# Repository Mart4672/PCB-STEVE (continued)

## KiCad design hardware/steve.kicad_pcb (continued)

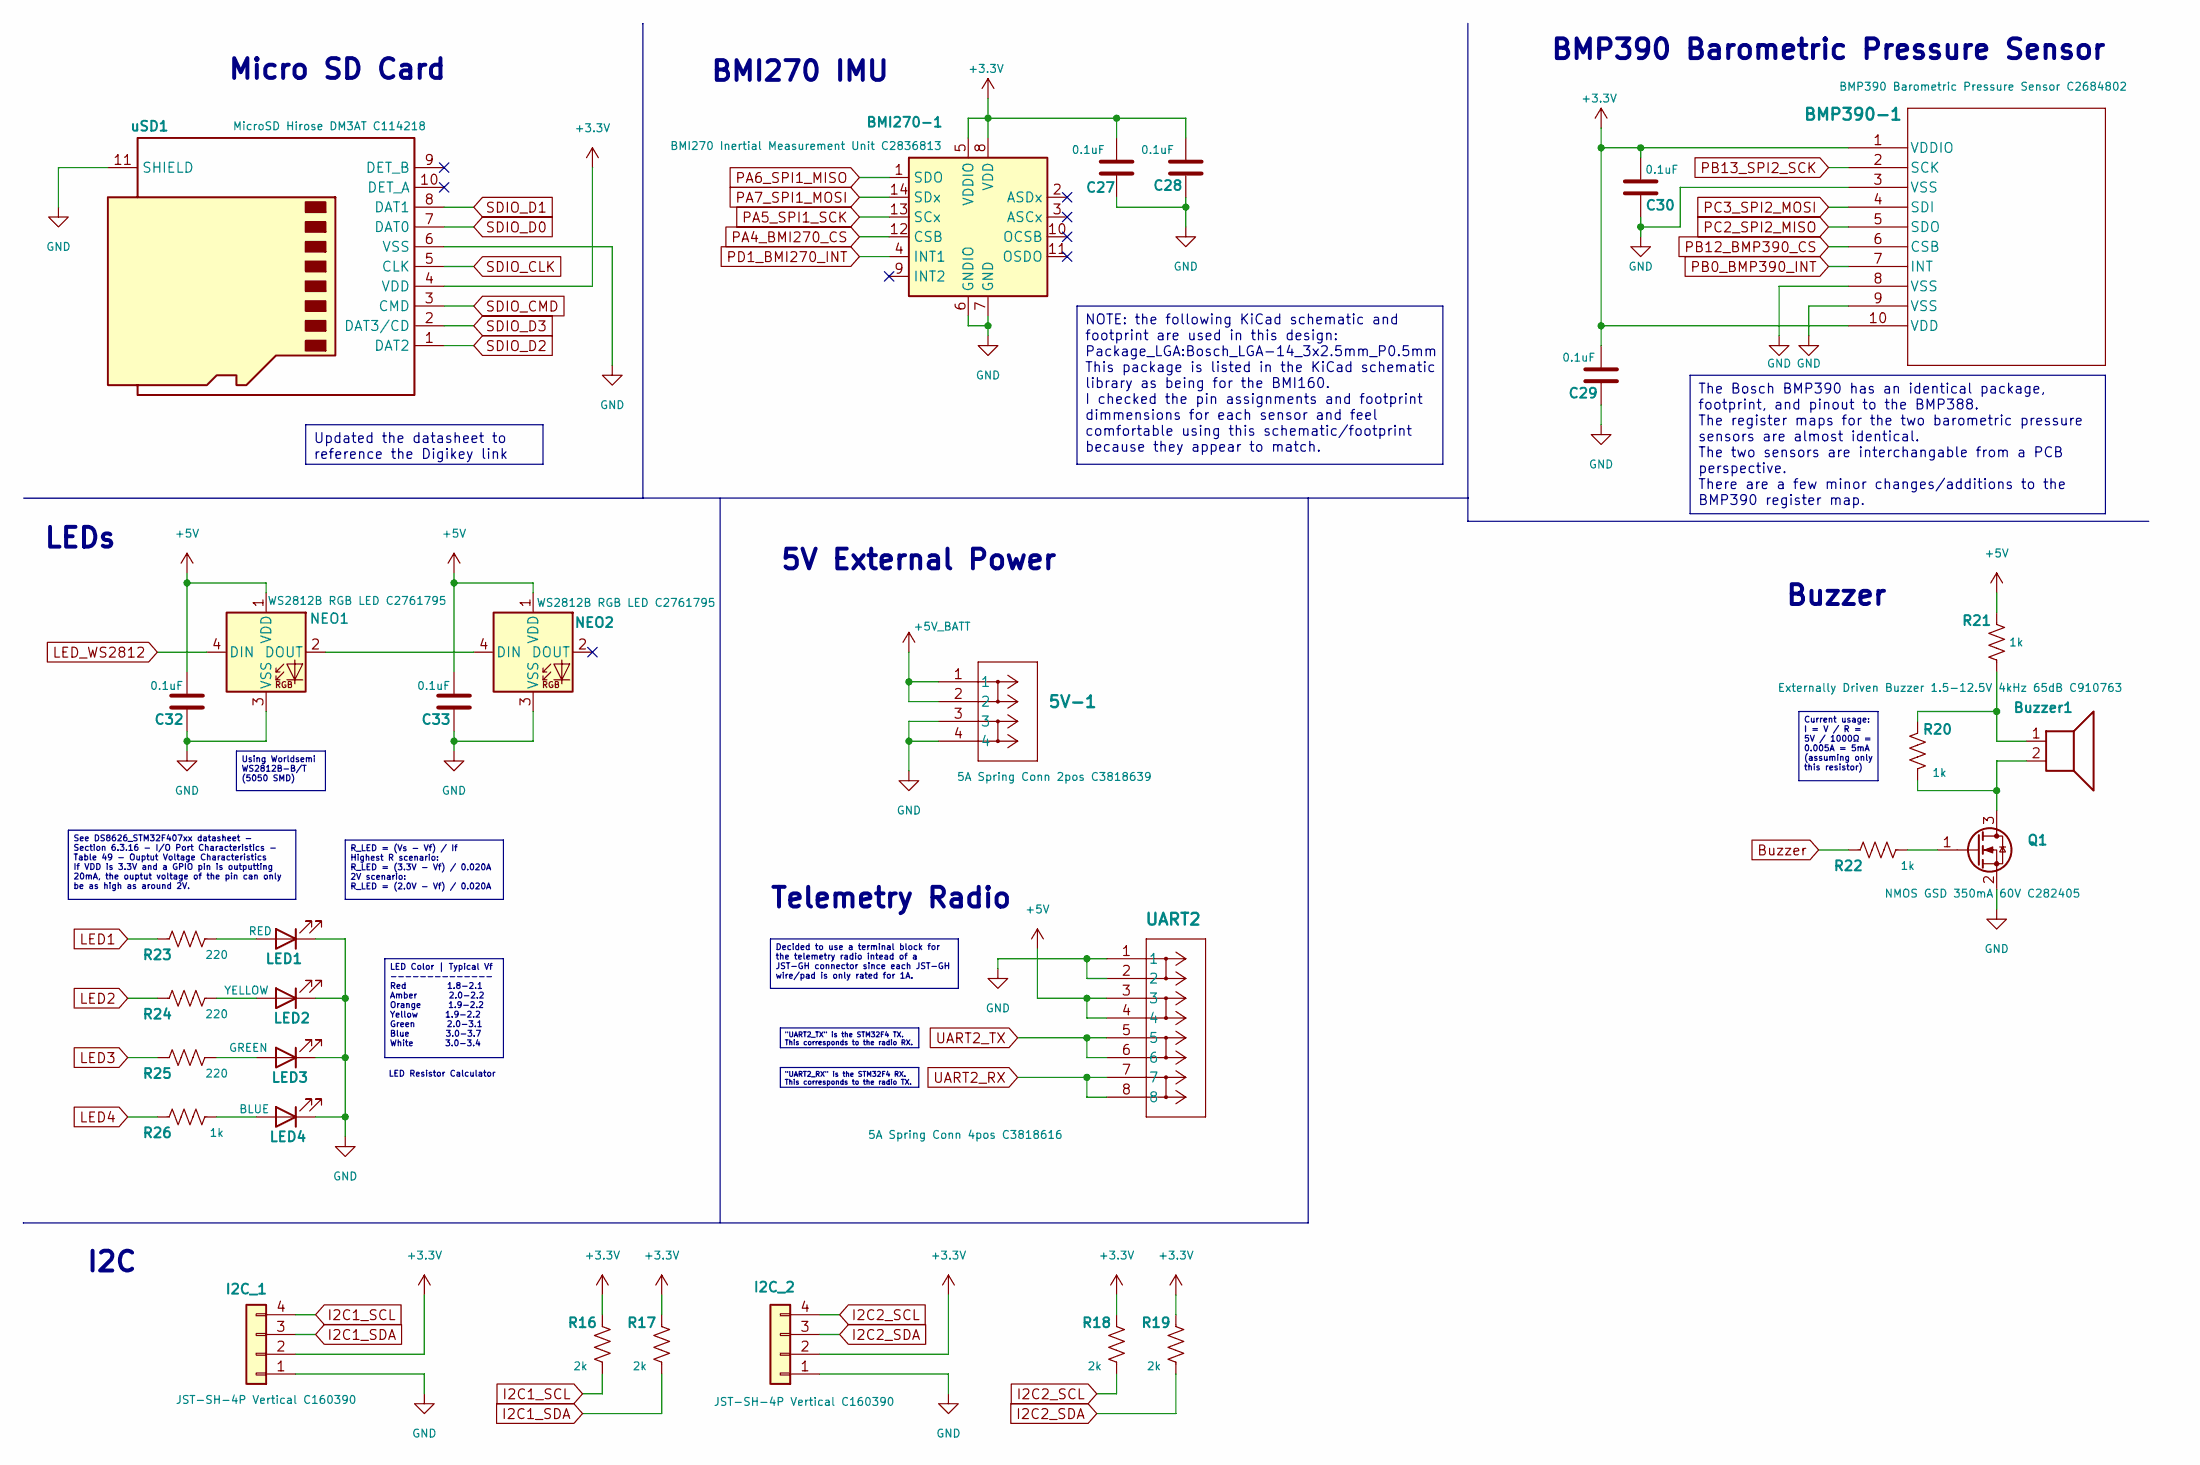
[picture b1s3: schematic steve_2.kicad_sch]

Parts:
5V-1: 5A Spring Conn 2pos C3818639; CONN_1814498_TerminalBlock-1770885-2pos
BMI270-1: BMI270 Inertial Measurement Unit C2836813; Bosch_LGA-14_3x2.5mm_P0.5mm
BMP390-1: BMP390 Barometric Pressure Sensor C2684802; QFN_BMP388_BOS
Buzzer1: Externally Driven Buzzer 1.5-12.5V 4kHz 65dB C910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; Buzzer_Murata_PKMCS0909E
C27, C28, C29, C30, C32, C33: 0.1uF; C_0603_1608Metric
I2C_1, I2C_2: JST-SH-4P Vertical C160390; JST-SH_BM04B-SRSS-TB_1x04_Vertical_P1.00mm
LED1: RED; LED_0603_1608Metric
LED2: YELLOW; LED_0603_1608Metric
LED3: GREEN; LED_0603_1608Metric
LED4: BLUE; LED_0603_1608Metric
NEO1, NEO2: WS2812B RGB LED C2761795; LED_WS2812B_PLCC4_5.0x5.0mm_P3.2mm
Q1: NMOS GSD 350mA 60V C282405; SOT-23
R16, R17, R18, R19: 2k; R_0603_1608Metric
R20, R21, R22, R26: 1k; R_0603_1608Metric
R23, R24, R25: 220; R_0603_1608Metric
UART2: 5A Spring Conn 4pos C3818616; CONN_1814582_TerminalBlock_1770979_4pos_Vertical
uSD1: MicroSD Hirose DM3AT C114218; microSD_3D_HC_Hirose_DM3AT-SF-PEJM5

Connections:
+3.3V: BMI270-1.5 (VDDIO), BMI270-1.8 (VDD), BMP390-1.1 (VDDIO), BMP390-1.10 (VDD), C27.1, C28.1, C29.1, C30.1, I2C_1.2, I2C_2.2, R16.2, R17.2, R18.2, R19.2, uSD1.4 (VDD); also elsewhere on the board
+5V: C32.1, C33.1, NEO1.1 (VDD), NEO2.1 (VDD), R21.2, UART2.3, UART2.4; also elsewhere on the board
+5V_BATT: 5V-1.1, 5V-1.2; also elsewhere on the board
Buzzer: R22.1; also elsewhere on the board
GND: 5V-1.3, 5V-1.4, BMI270-1.6 (GNDIO), BMI270-1.7 (GND), BMP390-1.3 (VSS), BMP390-1.8 (VSS), BMP390-1.9 (VSS), C27.2, C28.2, C29.2, C30.2, C32.2, C33.2, I2C_1.1, I2C_2.1, LED1.1 (K), LED2.1 (K), LED3.1 (K), LED4.1 (K), NEO1.3 (VSS), NEO2.3 (VSS), Q1.2 (S), UART2.1, UART2.2, uSD1.6 (VSS), uSD1.11 (SHIELD); also elsewhere on the board
I2C1_SCL: I2C_1.4, R16.1; also elsewhere on the board
I2C1_SDA: I2C_1.3, R17.1; also elsewhere on the board
I2C2_SCL: I2C_2.4, R18.1; also elsewhere on the board
I2C2_SDA: I2C_2.3, R19.1; also elsewhere on the board
LED1: R23.1; also elsewhere on the board
LED2: R24.1; also elsewhere on the board
LED3: R25.1; also elsewhere on the board
LED4: R26.1; also elsewhere on the board
LED_WS2812: NEO1.4 (DIN); also elsewhere on the board
unnamed: Buzzer1.1, R20.2, R21.1
unnamed: LED1.2 (A), R23.2
unnamed: LED2.2 (A), R24.2
unnamed: LED3.2 (A), R25.2
unnamed: LED4.2 (A), R26.2
unnamed: NEO1.2 (DOUT), NEO2.4 (DIN)
unnamed: Buzzer1.2, Q1.3 (D), R20.1
unnamed: Q1.1 (G), R22.2
PA4_BMI270_CS: BMI270-1.12 (CSB); also elsewhere on the board
PA5_SPI1_SCK: BMI270-1.13 (SCx); also elsewhere on the board
PA6_SPI1_MISO: BMI270-1.1 (SDO); also elsewhere on the board
PA7_SPI1_MOSI: BMI270-1.14 (SDx); also elsewhere on the board
PB0_BMP390_INT: BMP390-1.7 (INT); also elsewhere on the board
PB12_BMP390_CS: BMP390-1.6 (CSB); also elsewhere on the board
PB13_SPI2_SCK: BMP390-1.2 (SCK); also elsewhere on the board
PC2_SPI2_MISO: BMP390-1.5 (SDO); also elsewhere on the board
PC3_SPI2_MOSI: BMP390-1.4 (SDI); also elsewhere on the board
PD1_BMI270_INT: BMI270-1.4 (INT1); also elsewhere on the board
SDIO_CLK: uSD1.5 (CLK); also elsewhere on the board
SDIO_CMD: uSD1.3 (CMD); also elsewhere on the board
SDIO_D0: uSD1.7 (DAT0); also elsewhere on the board
SDIO_D1: uSD1.8 (DAT1); also elsewhere on the board
SDIO_D2: uSD1.1 (DAT2); also elsewhere on the board
SDIO_D3: uSD1.2 (DAT3/CD); also elsewhere on the board
UART2_RX: UART2.7, UART2.8; also elsewhere on the board
UART2_TX: UART2.5, UART2.6; also elsewhere on the board

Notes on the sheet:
BMP390 Barometric Pressure Sensor
Micro SD Card
LEDs
BMI270 IMU
5V External Power
LED Resistor Calculator
Buzzer
Telemetry Radio
I2C
LED Color | Typical Vf -------------- Red 1.8-2.1 Amber 2.0-2.2 Orange 1.9-2.2 Yellow 1.9-2.2 Green 2.0-3.1 Blue 3.0-3.7 White 3.0-3.4
See DS8626_STM32F407xx datasheet - Section 6.3.16 - I/O Port Characteristics - Table 49 - Ouptut Voltage Characteristics If VDD is 3.3V and a GPIO pin is outputting 20mA, the ouptut voltage of the pin can only be as high as around 2V.
Using Worldsemi WS2812B-B/T (5050 SMD)
Decided to use a terminal block for the telemetry radio intead of a JST-GH connector since each JST-GH wire/pad is only rated for 1A.
"UART2_TX" is the STM32F4 TX. This corresponds to the radio RX.
Current usage: I = V / R = 5V / 1000Ω = 0.005A = 5mA (assuming only this resistor)
NOTE: the following KiCad schematic and footprint are used in this design: Package_LGA:Bosch_LGA-14_3x2.5mm_P0.5mm This package is listed in the KiCad schematic library as being for the BMI160. I checked the pin assignments and footprint dimmensions for each sensor and feel comfortable using this s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
Updated the datasheet to reference the Digikey link
"UART2_RX" is the STM32F4 RX. This corresponds to the radio TX.
The Bosch BMP390 has an identical package, footprint, and pinout to the BMP388. The register maps for the two barometric pressure sensors are almost identical. The two sensors are interchangable from a PCB perspective. There are a few minor changes/additions to the BMP390 register map.
R_LED = (Vs - Vf) / If Highest R scenario: R_LED = (3.3V - Vf) / 0.020A 2V scenario: R_LED = (2.0V - Vf) / 0.020A

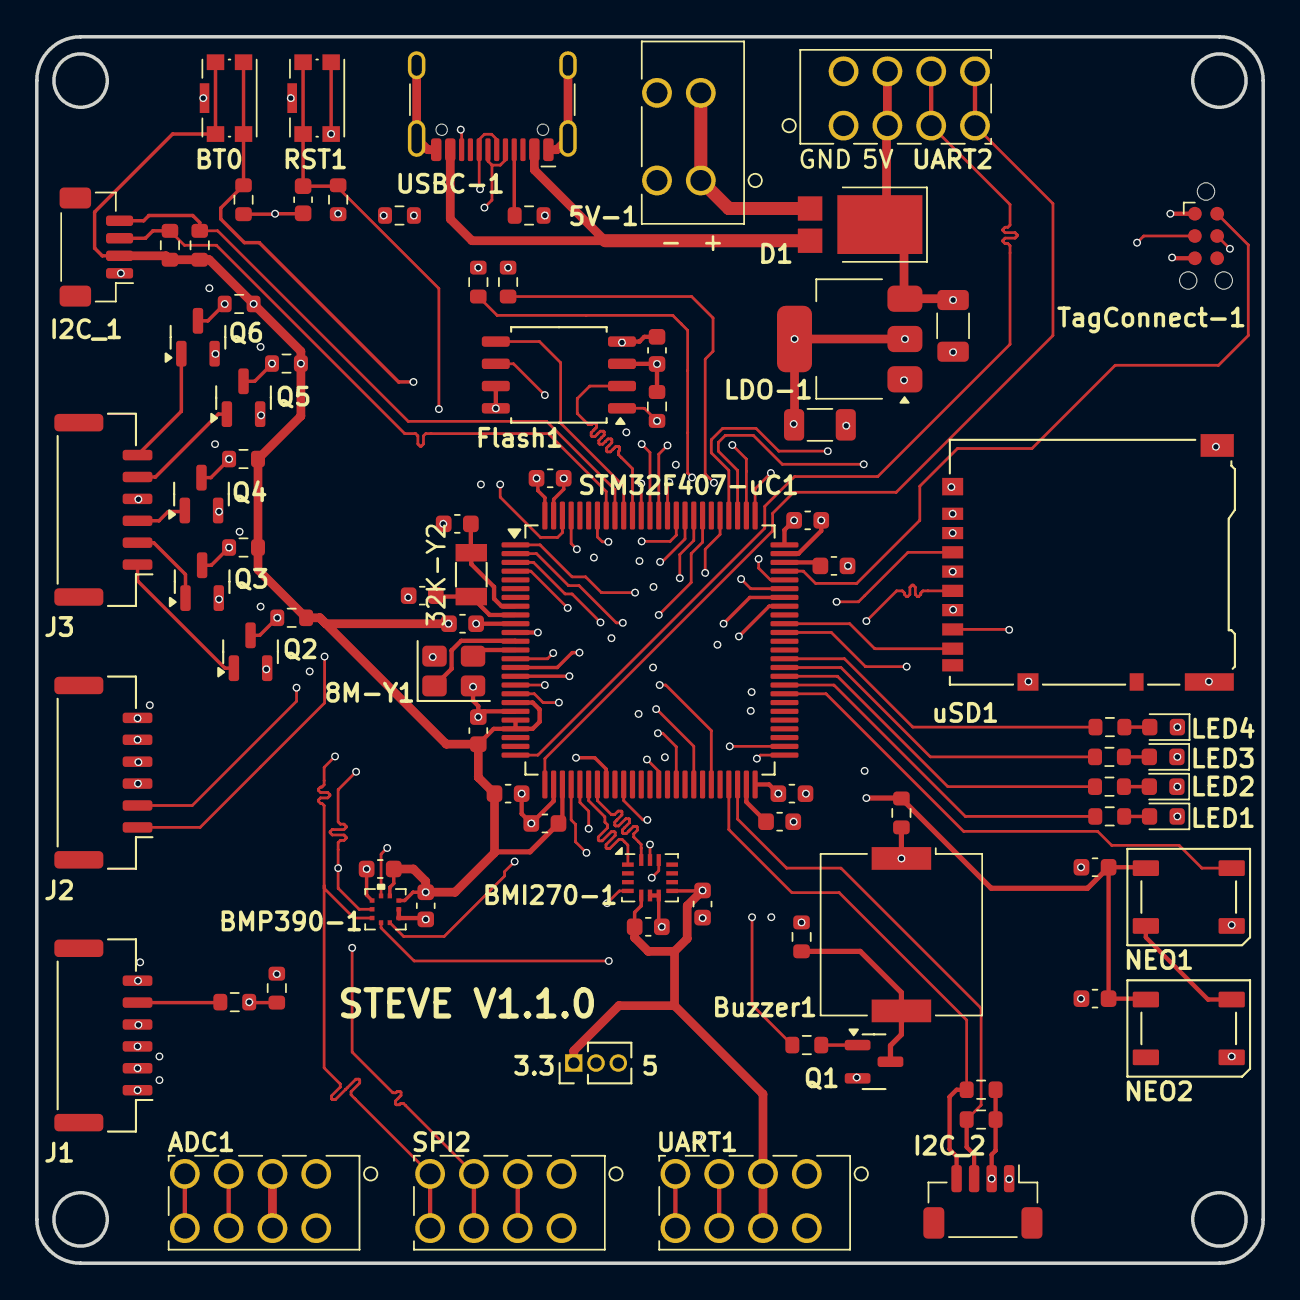
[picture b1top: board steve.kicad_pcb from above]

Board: 6 copper layers, 70.0 x 70.0 mm, 83 parts (0 on the bottom side), 87 nets.

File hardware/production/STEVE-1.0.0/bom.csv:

Designator,Footprint,Quantity,Value,LCSC Part #
32K-Y2,Crystal_SMD_3215-2Pin_3.2x1.5mm,1,32.768kHz Crystal 12.5pf C90944,
5V-1,CONN_1814498_TerminalBlock-1770885-2pos,1,5A Spring Conn 2pos C3818639,
8M-Y1,Crystal_SMD_3225-4Pin_3.2x2.5mm,1,8MHz Crystal 10pf C400090,
"ADC1, SPI2, UART1, UART2",CONN_1814582_TerminalBlock_1770979_4pos_Vertical,4,5A Spring Conn 4pos C3818616,
BMI270-1,Bosch_LGA-14_3x2.5mm_P0.5mm,1,BMI270 Inertial Measurement Unit C2836813,
BMP390-1,QFN_BMP388_BOS,1,BMP390 Barometric Pressure Sensor C2684802,
"BT0, RST1",SW_Push_3D_1P1T-SH_NO_CK_KMR2xxG,2,Button KMR221G C72443,
BUZZER1,Buzzer_Murata_PKMCS0909E,1,Externally Driven Buzzer 1.5-12.5V 4kHz 65dB C910763,
"C1, C2",0603,2,2.2uF,
"C10, C11, C27, C28, C29, C30, C31, C32, C33, C7, C8, C9",0603,12,0.1uF,
C12,0603,1,4.7uF,
"C13, C14",0603,2,1.0uF,
"C25, C26",1206,2,1.0uF,
"C5, C6",0603,2,5pF,
D1,PDS1040CTL-13_PowerDI-5,1,10A/5A Schottky Diode Arr C780876,
FLASH1,SOIC-8_5.23x5.23mm_P1.27mm_3D,1,W25Q128JVSIQ 128Mb SPI Flash C97521,
"I2C_1, I2C_2",JST-SH_BM04B-SRSS-TB_1x04_Vertical_P1.00mm,2,JST-SH-4P Vertical C160390,
"J1, J2, J3",JST_GH_BM06B-GHS-TBT_1x06-1MP_P1.25mm_Vertical,3,JST GH 6P Vertical 1A C189892,
LDO-1,SOT-223-3_TabPin2,1,3.3V 1A Lin Reg C15578,
LED1,0603,1,RED,
LED2,0603,1,YELLOW,
LED3,0603,1,GREEN,
LED4,0603,1,BLUE,
"NEO1, NEO2",LED_WS2812B_PLCC4_5.0x5.0mm_P3.2mm,2,WS2812B RGB LED C2761795,
"Q1, Q2, Q3, Q4, Q5, Q6",SOT-23,6,NMOS GSD 350mA 60V C282405,
"R1, R15",0603,2,100k,
"R11, R12",0603,2,22,
"R13, R14",0603,2,5.1k,
"R16, R17, R18, R19",0603,4,2k,
R2,0603,1,4.7k,
"R20, R21, R22, R26",0603,4,1k,
"R23, R24, R25",0603,3,220,
"R3, R4, R5, R6, R7",0603,5,10k,
R8,0603,1,422k 1%,
R9,0603,1,100k 0.5%,
STM32F407-UC1,LQFP-100_14x14mm_P0.5mm,1,STM32F407VGTx Microcontroller C12345,
USBC-1,USB_C_Receptacle_3D_HCTL_HC-TYPE-C-16P-01A,1,USB-C Receptacle 16P C3025063,
USD1,microSD_3D_HC_Hirose_DM3AT-SF-PEJM5,1,MicroSD Hirose DM3AT C114218,

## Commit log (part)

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2024-09-30 Added STEVE summary, started schematic
    Added STEVE info section to README. Added STEVE V1 Planned Hardware list to README. Started board schematic using KiCad STM32F407VG 100 pin footprint
2024-10-06 Added 5V reg and other components
    Added 5V regulator circuit to schematic. Added project libraries for imported symbols and footprints. Added additional components to schematic.
2025-04-06 import BMP388, add BMP388 to pcb and sch
    Import BMP388 symbol and footprint to project imports dir. Add BMP388 symbol to schematic and footprint to pcb.
2025-04-13 Finished sensor, flash, and SD card in schematic; Updated README for remaining items
    Finished BMI270 and BMP390, Flash storage, and microSD card in schematic; Updated README for remaining items
2025-04-14 Add components to schematic; fix existing ones
    Added additional components to schematic such as IO connectors. Replaced the 10A TO-263-2 diode rectifiers with much smaller 5A ones.
    Other various fixes.
2025-04-19 Added buzzer and LEDs to schematic
    Added buzzer and LEDs (4 regular and 2 WS2812B) to schematic. Minor schematic fixes such as PMIC enable pin voltage divider.
2025-04-20 Removed PSM board components; added power conn; fixed telem conn
    Moved PSM board components to the PSM board schematic.
    Added a connector for the regulated 5V input to STEVE that comes from the PSM board.
    Changed the radio telemetry connector to a 4 pin screwless terminal block to mitigate current limit concerns with the previous connector.
2025-04-27 Finished schematic
    Finished schematic - 3D model fixes using custom imports, all important parts sourced, additional GPIO/bus pins broken out, PSM board signals broken out, battery voltage sense line added.
2025-05-04 started component layout
    started component layout - attempting to use a 60x60mm board size
2025-05-08 finished initial component layout
2025-05-08 update flash chip 3D model; update to KiCad 9.0.2
    update flash chip 3D model with the new name used in KiCad 9.0.2
    Updated project to KiCad 9.0.2 (latest version)
2025-05-12 use 50x50mm board
2025-05-12 Add schematic PDF
    Add schematic PDF to newly created share folder in
    CURRENT_PROJECT_DIR/hardware
2025-05-13 started routing the PCB
    started routing the PCB - some components moved a bit. Added GND fill/pour on top and bottom planes, adding extra GND trace width where needed. Also routed short power traces on the top layer. The US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
2025-05-14 added first length matched SPI sets
    added first length matched SPI sets for the Flash chip and the BMI270. Still need to finish routing the BMI270 and other footprints that use SPI
2025-05-18 Finished routing traces
    Finished routing traces. Also added extra ground vias to stitch the ground planes together. Lessons for next time: power pads (on a microcontroller or other) should immediately get a via; passives ca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
2025-05-18 Increase text to 1mm
    Increase text length/width to 1mm and line thickness to 0.153mm to match fab capabilities and rules. All capacitor and resistor designators have been hidden to reduce silkscreen clutter.
2025-05-24 Added Custom Design Rules for JLC; fixed DRC errors
    Added Custom Design Rules for JLC based on a community created custom ruleset.
    Fixed DRC errors that the custom JLC rules pointed out. Updated project constraints to not throw extra errors.
2025-05-24 Add text to board
    Add text to board silkscreen
2025-05-24 Generated JLC production files
    Generated JLC production files using the "Fabrication Toolkit" (JLC) plugin
    STEVE_1.0.0.zip created
    BOM and Placement CSVs also created, but not included due to the gitignore
2025-05-24 Schematic and Board fixes for Mfg
    Schematic and Board fixes for Manufacturing. Added LCSC/JLC part numbers to values in schematic for BOM processing. Updated schematic fields. Added GND to each PSM connector. Brought PSM connector fi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
2025-05-25 Updated production files
    Generated new production files now that all major components have a JLC part number added to their value and the J1-J3 connectors have been changed.
2025-05-25 Add JLC Quote data for STEVE V1.0.0
    Save screenshots of all JLC quote line items for ordering STEVE V1.0.0
    Does not include the true cost of all major components since many were purchased separately before this point.
    Also does not include the possible price of "baking" AKA drying the WS2812 LEDs (~$7.50).
    Readme updated.
2025-05-25 Add STEVE V1.0.0 board pictures to share folder
    Add STEVE V1.0.0 board pictures to share/STEVE_V1.0.0 folder
2025-05-25 Regenerated STEVE V1.0.0 Schematic
    Regenerated STEVE V1.0.0 Schematic (since it was updated a bit). Moved the schematic to the STEVE_V1.0.0 folder
2025-05-25 updated README
    updated README for STEVE V1.0.0
2025-05-25 Fixed all ERC issues; fixed important DRC issues
    Fixed all ERC Errors and Warnings in the schematic. Fixed all Errors and Warnings in the DRC for the board (Not counting JLC 4-Wire Kelvin test and plane thermal relief spoke errors that were manuall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
2025-05-30 Update board to 6 layers and single sided assembly
    Update board to 6 layers and single sided assembly (all components placed on the same side); all footprints given an initial placement
2025-06-01 Routed 6 layer board; DRC passes
    Finished routing the 6 layer board; All DRC issues resolved
2025-06-01 Created STEVE footprint; added image to PCB
    Created STEVE image footprint with KiCad bitmap image tool; added footprint to imported footprints library; manually added new footprint to PCB.
2025-06-01 Moved STEVE 1.0.0 production files to a named folder
    Moved STEVE 1.0.0 production files to a named folder for organization
2025-06-01 Generated STEVE 1.1.0 production files
    Generated STEVE 1.1.0 production files; files in hardware/production/STEVE-1.1.0
2025-06-01 Update gitignore to allow csv files to be saved
    Update gitignore to allow csv files to be saved.
    STEVE 1.0.0 and 1.1.0 csv files are now tracked.
2025-06-01 Add STEVE 1.1.0 Schematic PDF and board pictures
    Add STEVE 1.1.0 Schematic PDF and board pictures (renders from 3D viewer)
2025-06-01 Added costed down bom and positions files
    Added costed down bom and positions files. The costed_down_1 csv files have the easy through-hole components removed, specifically the screwless terminal blocks
2025-06-02 Added quote pictures; updated README
    Added quote pictures; updated README.
    STEVE 1.1.0 has been ordered
